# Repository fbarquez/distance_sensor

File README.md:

# Ultrasonic Distance Sensor System – Abstandssensor

## Usage Notice

This project was developed as part of the module “Information Technology / Networked Systems” in the Bachelor's program in Information and Communication Engineering.

- Repository is archived and read-only.
- Not licensed for reuse, redistribution, or modification.
- For demonstration and educational reference only.
- Licensed under **UNLICENSED**.

> Developed by **Fbarquez** - HTW Berlin, 2021

---

## About the Project

This project is a **microcontroller-based distance measuring system** designed to support social distancing during the COVID-19 pandemic. The sensor system detects nearby objects using **ultrasound technology** and triggers **visual and acoustic alerts** when the safety distance is not maintained.

> **Main goal:** Help individuals monitor and maintain the recommended 1.5–2 meters distance to prevent virus transmission.

---

## Media Preview

### [▶ Watch Demo Video](https://www.dropbox.com/scl/fi/pl3xh61fnlcbmjqz21ddf/Abstandssensor_video_FB.mp4?rlkey=nnty2kcn74rb1pb28xz7tbtho&st=4qxa9l1h&raw=1)

> A live demo showing the behavior of the sensor system in real conditions.

---

## Project Objectives

- Measure distances in real-time using the **HC-SR04 ultrasonic sensor**
- Visually indicate proximity using **LEDs** (green = safe, red = warning)
- Trigger **buzzer** alert when distance is dangerously short
- Display distance on a **20x4 LCD display**
- **Transmit data via Bluetooth** to a mobile app
- Provide a **portable, reliable, and affordable** prevention tool

---

## Hardware Overview

| Component              | Description                               |
|------------------------|-------------------------------------------|
| PIC16F1936             | 8-bit microcontroller (main control unit) |
| LCD 20x4               | Visual distance output                    |
| HC-SR04                | Ultrasonic distance sensor                |
| LEDs                   | Red (short), Green (safe) alerts          |
| Buzzer                 | Audio alert for danger distance           |
| HC-05 Bluetooth Module | Wireless transmission to Android          |
| External Power Supply  | 5V regulated                              |

> Schematics and PCB were designed using **EAGLE** software.

---

## System Logic

```text
              +--------------------+
              |    Ultrasonic      |
              |     Sensor         |
              +--------+-----------+
                       |
             Measures Time of Echo
                       |
                       v
        +--------------+--------------+
        |     PIC16F1936 MCU          |
        | (Distance Calculation Logic)|
        +-------+----------+----------+
                |          |         
         +------v--+  +----v-----+ 
         |   LCD    |  | Bluetooth| --> Smartphone App
         +----------+  +----------+
             |
     +-------+--------+
     |      LEDs      |
     |   Buzzer Alarm |
     +----------------+
````

The MCU uses **Timer1** to measure the echo pulse from the sensor. Based on the measured time, it calculates distance using:

```
distance_cm = duration / 58
```

Depending on the result:

* **> 50 cm** → Green LED ON (safe)
* **30–50 cm** → Red LED ON (warning)
* **< 30 cm** → Red LED + Buzzer ON (danger)

---

## How It Works

1. **Startup**: LCD displays intro text → system initializes
2. **Sensor trigger**: Sends 10μs pulse to HC-SR04 TRIG
3. **Echo measured**: Timer1 starts on echo rise, stops on fall
4. **Distance calculation**: Converts time into cm
5. **LED + Buzzer logic**: Executes based on thresholds
6. **LCD display**: Shows distance in cm
7. **Bluetooth transmission**: Sends data to Android app

---

## Project Structure

```
Abstandsssensor.X/
├── main.c                   # Main program logic
├── lcd 20x4_1.h             # Custom LCD display driver
├── mcc_generated_files/     # Microchip Code Configurator auto-generated code
├── MyConfig.mc3             # MCC configuration file
├── nbproject/               # MPLAB X project configuration
├── Makefile                 # Project build rules
├── .clang-format            # Code formatting configuration
├── build/, dist/, debug/    # Build artifacts (can be ignored or gitignored)
├── eagle/
│   ├── Diseño .brd          # PCB layout
│   └── Diseño .sch          # Schematic diagram
```

---

## Features

* Real-time distance display on LCD
* Visual LED indication based on proximity
* Acoustic alarm for dangerous range
* Bluetooth communication with Android device
* Fully coded in C using **XC8** and **MPLAB X IDE**
* Clean code style with `.clang-format`
* Version-controlled with Git

---

## How to Build & Run

1. Open the project in **MPLAB X IDE**
2. Ensure you have:

   * XC8 compiler installed
   * MCC plugin enabled
3. Configure your hardware:

   * Connect HC-SR04 to RA0 (TRIG) and RA1 (ECHO)
   * Connect LEDs and Buzzer to PORTC
4. Program the PIC16F1936 using SNAP or PICKIT
5. Power on — the system is ready to operate

---

## Android App Integration

* The HC-05 Bluetooth module sends messages like:

  * `"DISTANCE: 045cm"`
  * `"ALARM: DANGEROUS"`
* App GUI made with **Bluetooth Electronics App**
* Enables real-time distance visualization on your phone

---

## Eagle Design Files

Schematic (`.sch`) and Board Layout (`.brd`) are included in the `eagle/` directory for PCB fabrication and review.

---

## Requirements

To build, program, or extend this project, you will need a set of development tools such as the MPLAB X IDE and the XC8 compiler.

Please refer to the [requirements.md](requirements.md) file for full details on the required software, versions, and links to official downloads.

---

## References

* [PIC16F1936 Datasheet](http://ww1.microchip.com/downloads/en/DeviceDoc/41364E.pdf)
* [HC-SR04 Datasheet](https://cdn.sparkfun.com/datasheets/Sensors/Proximity/HCSR04.pdf)
* [HC-05 Bluetooth](https://components101.com/sites/default/files/component_datasheet/HC-05)
* [HD44780 LCD](https://www.sparkfun.com/datasheets/LCD/HD44780.pdf)

---

For usage restrictions and legal information, see [NOTICE.md](NOTICE.md).

---

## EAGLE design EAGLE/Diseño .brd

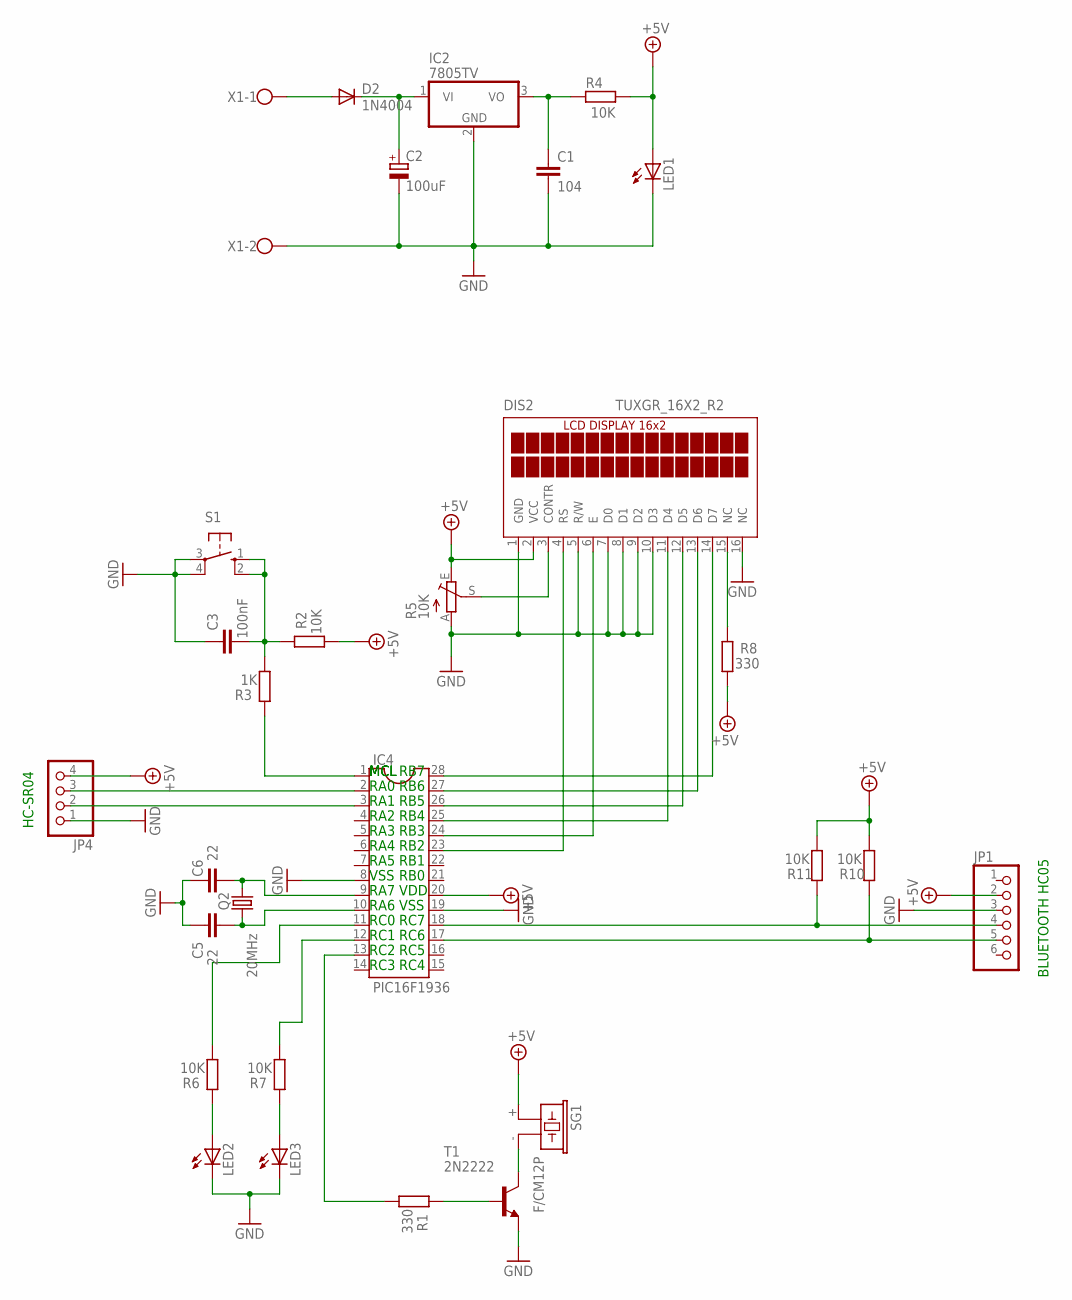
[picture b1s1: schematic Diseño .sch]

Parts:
C1: 104; C050-024X044
C2: 100uF; E5-5
C3: 100nF; C050-024X044
C5, C6: 22; C050-024X044
D2: 1N4004; DO41-10
DIS2: TUXGR_16X2_R2
IC2: 7805TV; TO220V
IC4: PIC16F1936; DIL28S
JP1: PINHD-1X6; 1X06
JP4: PINHD-1X4; 1X04
LED1, LED2, LED3: LED3MM
Q2: 20MHz; HC49U-V
R1, R8: 330; 0207/10
R2, R4, R6, R7, R10, R11: 10K; 0207/10
R3: 1K; 0207/10
R5: 10K; CA9V
S1: 10-XX; B3F-10XX
SG1: F/CM12P
T1: 2N2222; TO92-EBC
X1: W237-102

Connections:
+5V: DIS2.2 (VCC), IC4.20, JP1.2, JP4.4, LED1.A, R2.1, R4.1, R5.E, R8.1, R10.1, R11.1, SG1.+ (1)
GND: C1.2, C2.-, C3.2, C5.2, C6.2, DIS2.1 (GND), DIS2.5 (R/W), DIS2.7 (D0), DIS2.8 (D1), DIS2.9 (D2), DIS2.10 (D3), DIS2.16 (NC), IC2.2 (GND), IC4.8, IC4.19, JP1.3, JP4.1, LED1.K (C), LED2.K (C), LED3.K (C), R5.A, S1.3, S1.4 (P1), T1.E, X1.2
unnamed: D2.A, X1.1
unnamed: IC4.1, R3.2
unnamed: R1.2, T1.B
unnamed: SG1.- (2), T1.C
unnamed: C3.1, R2.2, R3.1, S1.1 (S), S1.2 (S1)
unnamed: IC4.13, R1.1
unnamed: IC4.2, JP4.3
unnamed: DIS2.15 (NC), R8.2
unnamed: IC4.18, JP1.4, R11.2
unnamed: IC4.17, JP1.5, R10.2
unnamed: DIS2.11 (D4), IC4.25
unnamed: DIS2.12 (D5), IC4.26
unnamed: IC4.3, JP4.2
unnamed: LED2.A, R6.2
unnamed: DIS2.13 (D6), IC4.27
unnamed: DIS2.14 (D7), IC4.28
unnamed: DIS2.6 (E), IC4.24
unnamed: C5.1, IC4.10, Q2.1
unnamed: C6.1, IC4.9, Q2.2
unnamed: DIS2.4 (RS), IC4.23
unnamed: C2.+, D2.C, IC2.1 (VI)
unnamed: C1.1, IC2.3 (VO), R4.2
unnamed: LED3.A, R7.2
unnamed: IC4.11, R6.1
unnamed: IC4.12, R7.1
unnamed: DIS2.3 (CONTR), R5.S

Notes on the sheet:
BLUETOOTH HC05
MCL
RA0
RA1
RA2
RA3
RA4
RA5
VSS
RA7
RA6
RC0
RC1
RC2
RC3
RC4
RC5
RC6
RC7
VDD
RB0
RB1
RB2
RB3
RB4
RB5
RB6
RB7
HC-SR04

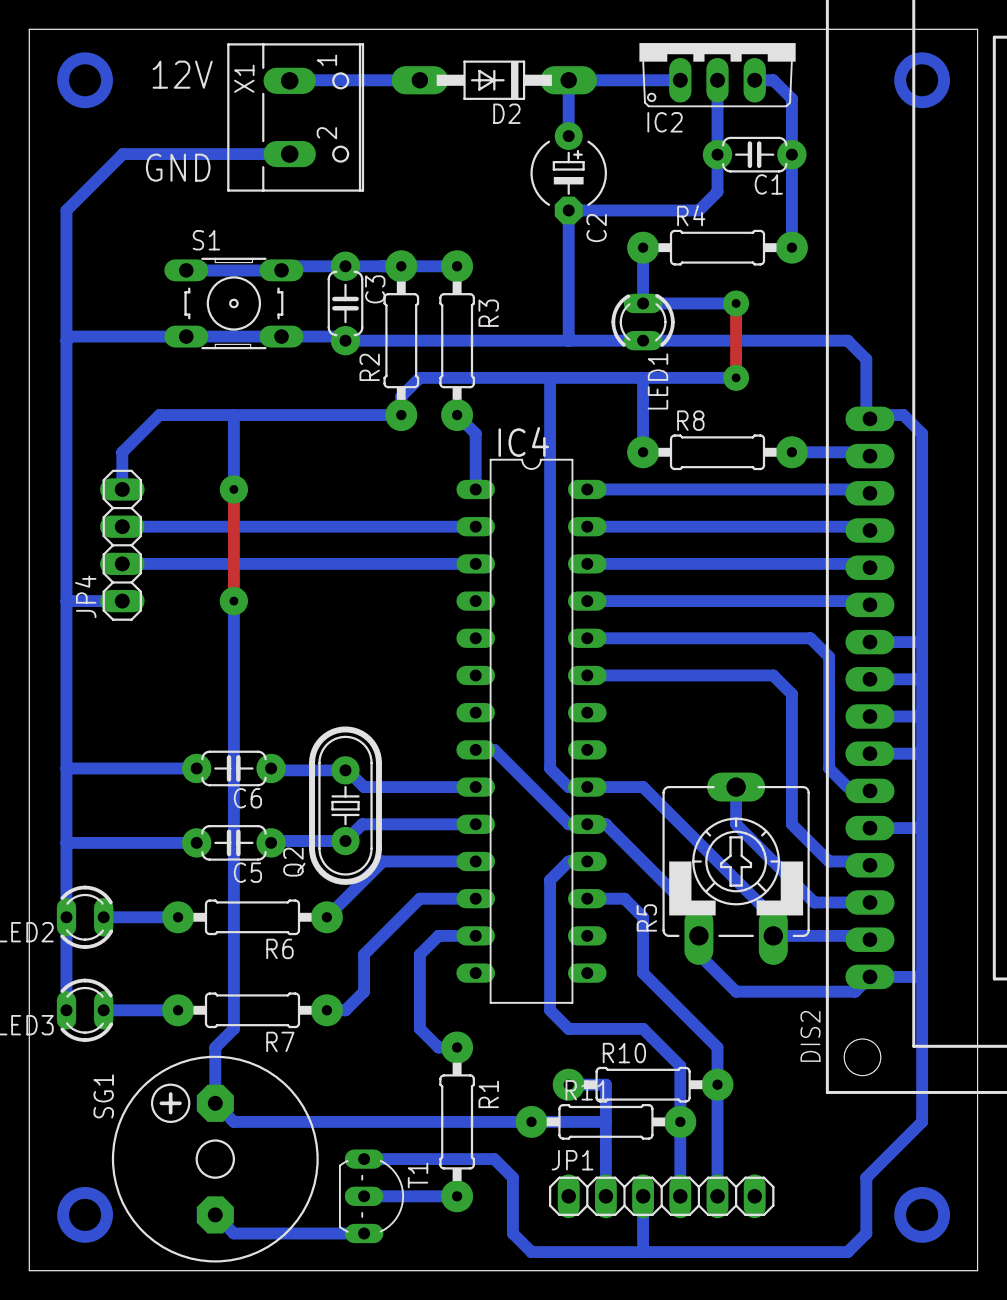
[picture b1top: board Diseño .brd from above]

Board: 2 copper layers, 64.8 x 84.8 mm, 29 parts (0 on the bottom side), 28 nets.

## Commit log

2025-05-29 Initial commit: upload of distance sensor project
2025-05-29 requirements
